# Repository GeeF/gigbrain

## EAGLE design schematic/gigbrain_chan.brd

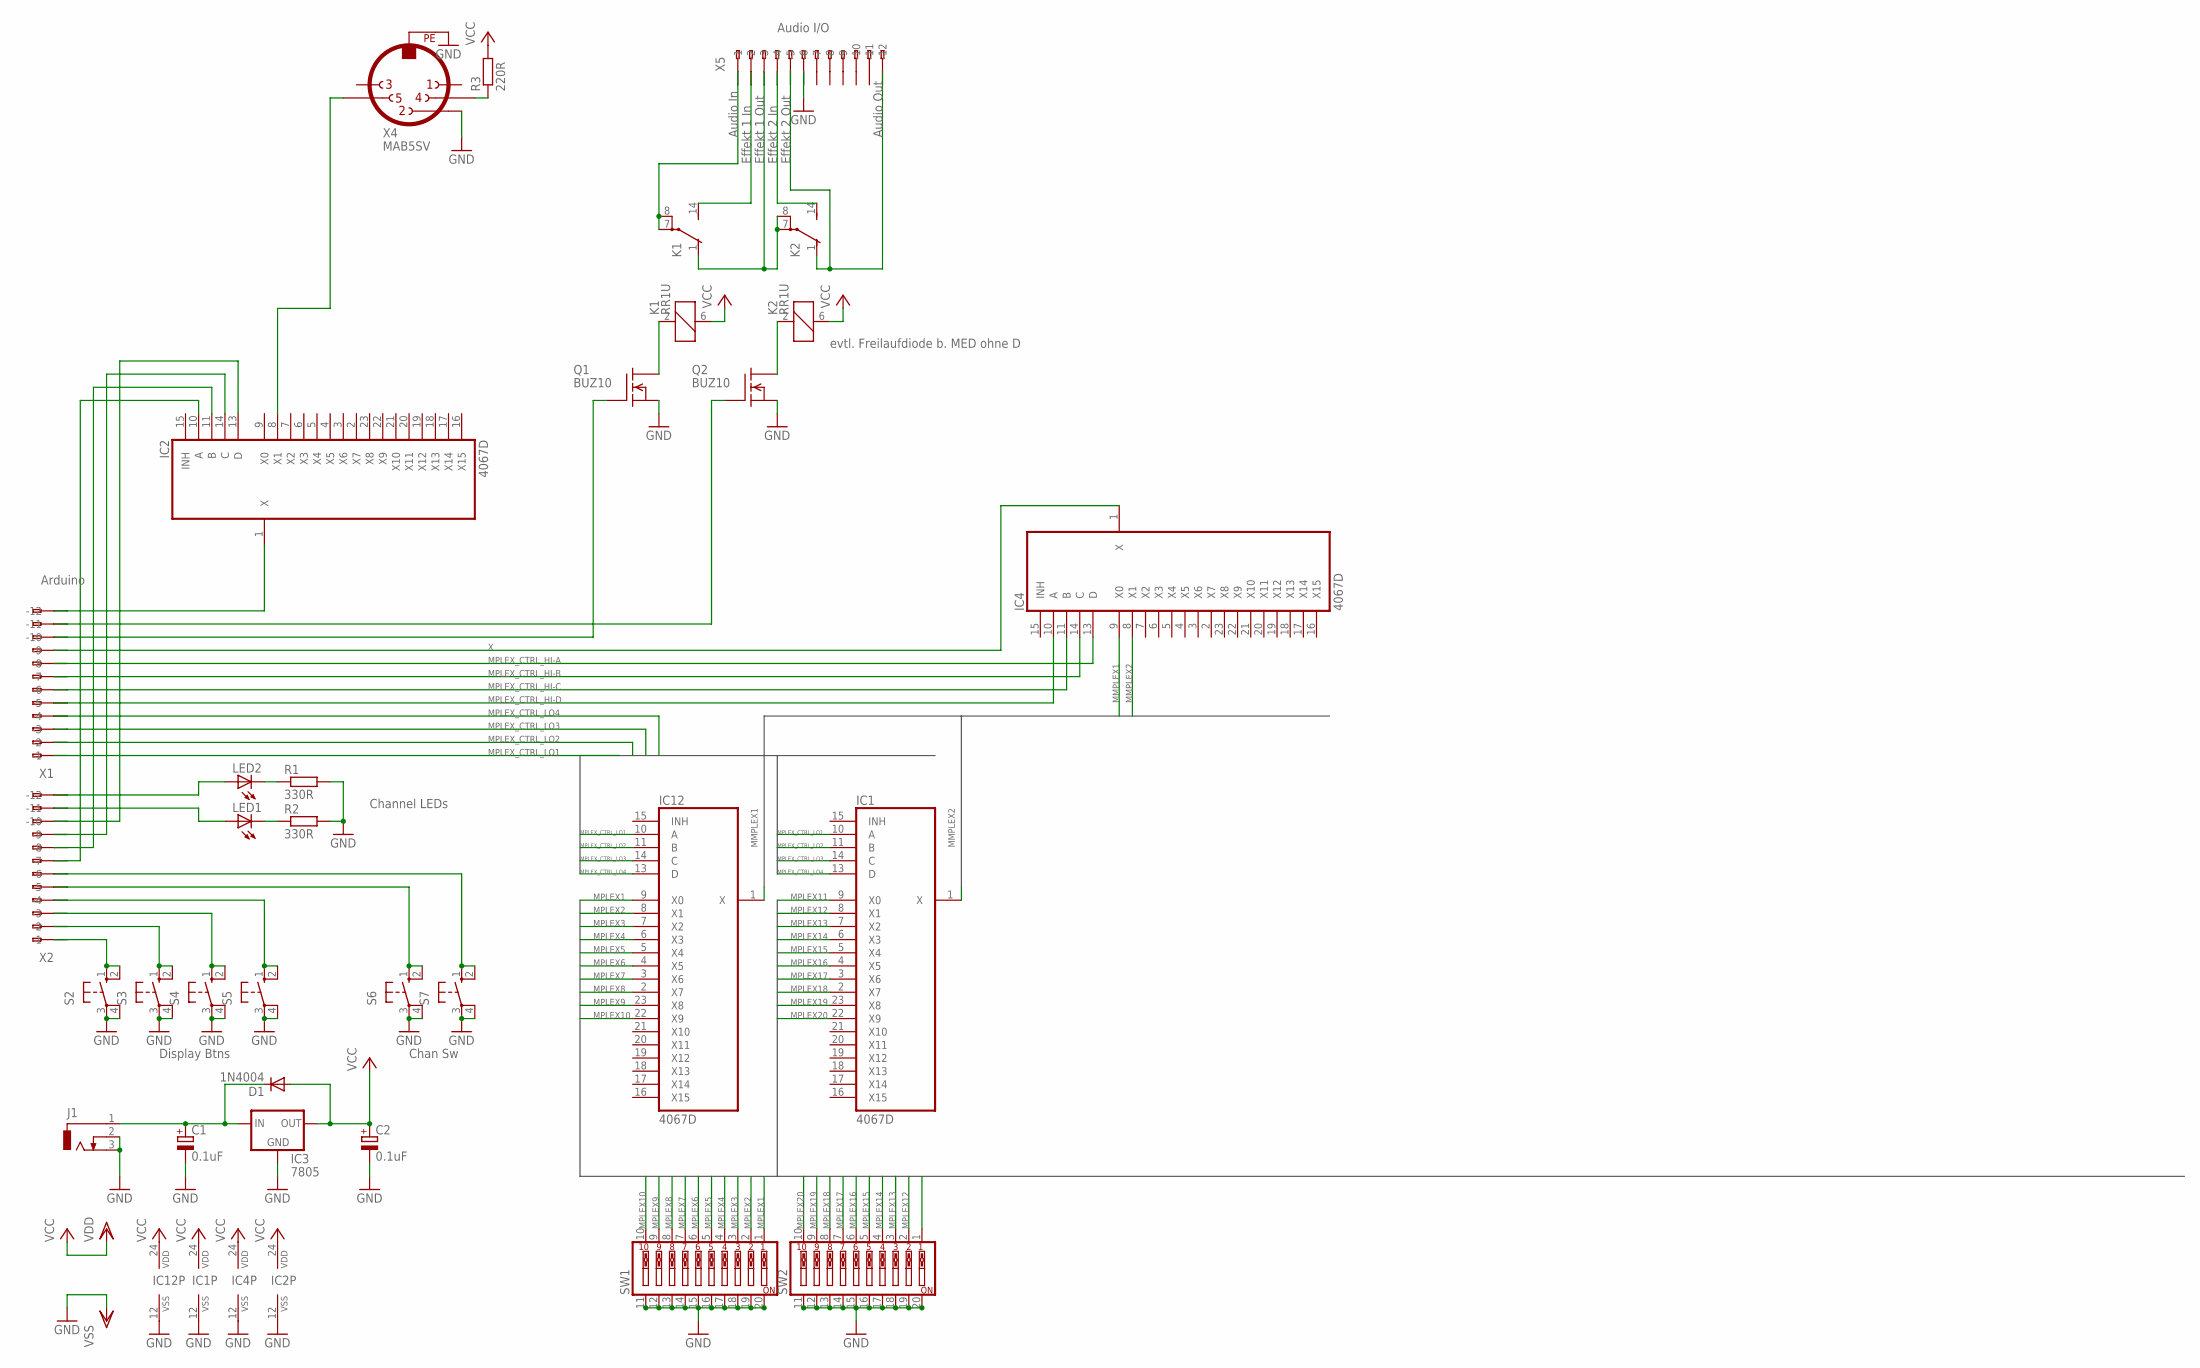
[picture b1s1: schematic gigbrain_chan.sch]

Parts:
C1, C2: 0.1uF; E2,5-5
D1: 1N4004; DO41-10
IC1, IC2, IC4, IC12: 4067D; SO24W
IC3: 7805; 78XXL
J1: DCJ0303
K1, K2: RR1U
LED1, LED2: LED3MM
Q1, Q2: BUZ10; TO220
R1, R2: 330R; 0204/7
R3: 220R; 0207/10
S2, S3, S4, S5, S6, S7: 10-XX; B3F-10XX
SW1, SW2: SW_DIP-10; EDG-10
X1, X2, X5: 233-512
X4: MAB5SV

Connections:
GND: C1.-, C2.-, IC1.12 (VSS), IC2.12 (VSS), IC3.GND, IC4.12 (VSS), IC12.12 (VSS), J1.2, J1.3, Q1.3 (S), Q2.3 (S), R1.2, R2.2, S2.3, S2.4 (P1), S3.3, S3.4 (P1), S4.3, S4.4 (P1), S5.3, S5.4 (P1), S6.3, S6.4 (P1), S7.3, S7.4 (P1), SW1.11, SW1.12, SW1.13, SW1.14, SW1.15, SW1.16, SW1.17, SW1.18, SW1.19, SW1.20, SW2.11, SW2.12, SW2.13, SW2.14, SW2.15, SW2.16, SW2.17, SW2.18, SW2.19, SW2.20, X4.2, X4.PE, X5.A6 (-6), X5.B6 (B-6)
MMPLEX1: IC4.9 (X0), IC12.1 (X)
MMPLEX2: IC1.1 (X), IC4.8 (X1)
MPLEX1: IC12.9 (X0), SW1.1
MPLEX2: IC12.8 (X1), SW1.2
MPLEX3: IC12.7 (X2), SW1.3
MPLEX4: IC12.6 (X3), SW1.4
MPLEX5: IC12.5 (X4), SW1.5
MPLEX6: IC12.4 (X5), SW1.6
MPLEX7: IC12.3 (X6), SW1.7
MPLEX8: IC12.2 (X7), SW1.8
MPLEX9: IC12.23 (X8), SW1.9
MPLEX10: IC12.22 (X9), SW1.10
MPLEX11: IC1.9 (X0), SW2.1
MPLEX12: IC1.8 (X1), SW2.2
MPLEX13: IC1.7 (X2), SW2.3
MPLEX14: IC1.6 (X3), SW2.4
MPLEX15: IC1.5 (X4), SW2.5
MPLEX16: IC1.4 (X5), SW2.6
MPLEX17: IC1.3 (X6), SW2.7
MPLEX18: IC1.2 (X7), SW2.8
MPLEX19: IC1.23 (X8), SW2.9
MPLEX20: IC1.22 (X9), SW2.10
MPLEX_CTRL_LO1: IC1.10 (A), IC12.10 (A), X1.A1 (-1), X1.B1 (B-1)
MPLEX_CTRL_LO2: IC1.11 (B), IC12.11 (B), X1.A2 (-2), X1.B2 (B-2)
MPLEX_CTRL_LO3: IC1.14 (C), IC12.14 (C), X1.A3 (-3), X1.B3 (B-3)
MPLEX_CTRL_LO4: IC1.13 (D), IC12.13 (D), X1.A4 (-4), X1.B4 (B-4)
unnamed: IC4.10 (A), X1.A5 (-5), X1.B5 (B-5)
unnamed: IC4.11 (B), X1.A6 (-6), X1.B6 (B-6)
unnamed: IC4.14 (C), X1.A7 (-7), X1.B7 (B-7)
unnamed: IC4.13 (D), X1.A8 (-8), X1.B8 (B-8)
unnamed: C1.+, D1.C, IC3.IN, J1.1
unnamed: IC2.8 (X1), X4.5
unnamed: S2.1 (S), S2.2 (S1), X2.A1 (-1), X2.B1 (B-1)
unnamed: S3.1 (S), S3.2 (S1), X2.A2 (-2), X2.B2 (B-2)
unnamed: S4.1 (S), S4.2 (S1), X2.A3 (-3), X2.B3 (B-3)
unnamed: S5.1 (S), S5.2 (S1), X2.A4 (-4), X2.B4 (B-4)
unnamed: S6.1 (S), S6.2 (S1), X2.A5 (-5), X2.B5 (B-5)
unnamed: S7.1 (S), S7.2 (S1), X2.A6 (-6), X2.B6 (B-6)
unnamed: R3.1, X4.4
unnamed: IC2.1 (X), X1.A12 (-12), X1.B12 (B-12)
unnamed: IC2.10 (A), X2.A7 (-7), X2.B7 (B-7)
unnamed: IC2.11 (B), X2.A8 (-8), X2.B8 (B-8)
unnamed: K2.1 (O), X5.A5 (-5), X5.A12 (-12), X5.B5 (B-5), X5.B12 (B-12)
unnamed: Q1.1 (G), X1.A10 (-10), X1.B10 (B-10)
unnamed: IC2.14 (C), X2.A9 (-9), X2.B9 (B-9)
unnamed: IC2.13 (D), X2.A10 (-10), X2.B10 (B-10)
unnamed: K1.2 (1), Q1.2 (D)
unnamed: K2.2 (1), Q2.2 (D)
unnamed: LED2.A, X2.A12 (-12), X2.B12 (B-12)
unnamed: LED1.A, X2.A11 (-11), X2.B11 (B-11)
unnamed: Q2.1 (G), X1.A11 (-11), X1.B11 (B-11)
unnamed: K1.7, K1.8, X5.A1 (-1), X5.B1 (B-1)
unnamed: K1.1 (O), K2.7, K2.8, X5.A3 (-3), X5.B3 (B-3)
unnamed: K1.14 (S), X5.A2 (-2), X5.B2 (B-2)
unnamed: K2.14 (S), X5.A4 (-4), X5.B4 (B-4)
unnamed: LED2.K (C), R1.1
unnamed: LED1.K (C), R2.1
VCC: C2.+, D1.A, IC1.24 (VDD), IC2.24 (VDD), IC3.OUT, IC4.24 (VDD), IC12.24 (VDD), K1.6 (2), K2.6 (2), R3.2
X: IC4.1 (X), X1.A9 (-9), X1.B9 (B-9)

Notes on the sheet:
Arduino
MPLEX_CTRL_HI-A
MPLEX_CTRL_HI-B
MPLEX_CTRL_HI-C
MPLEX_CTRL_HI-D
Display Btns
Chan Sw
Audio I/O
evtl. Freilaufdiode b. MED ohne D
Effekt 1 In
Effekt 1 Out
Effekt 2 In
Effekt 2 Out
Audio In
Audio Out
Channel LEDs

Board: 2 copper layers, 30 parts (0 on the bottom side), 60 nets, no tracks yet.

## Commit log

2013-08-28 initial
